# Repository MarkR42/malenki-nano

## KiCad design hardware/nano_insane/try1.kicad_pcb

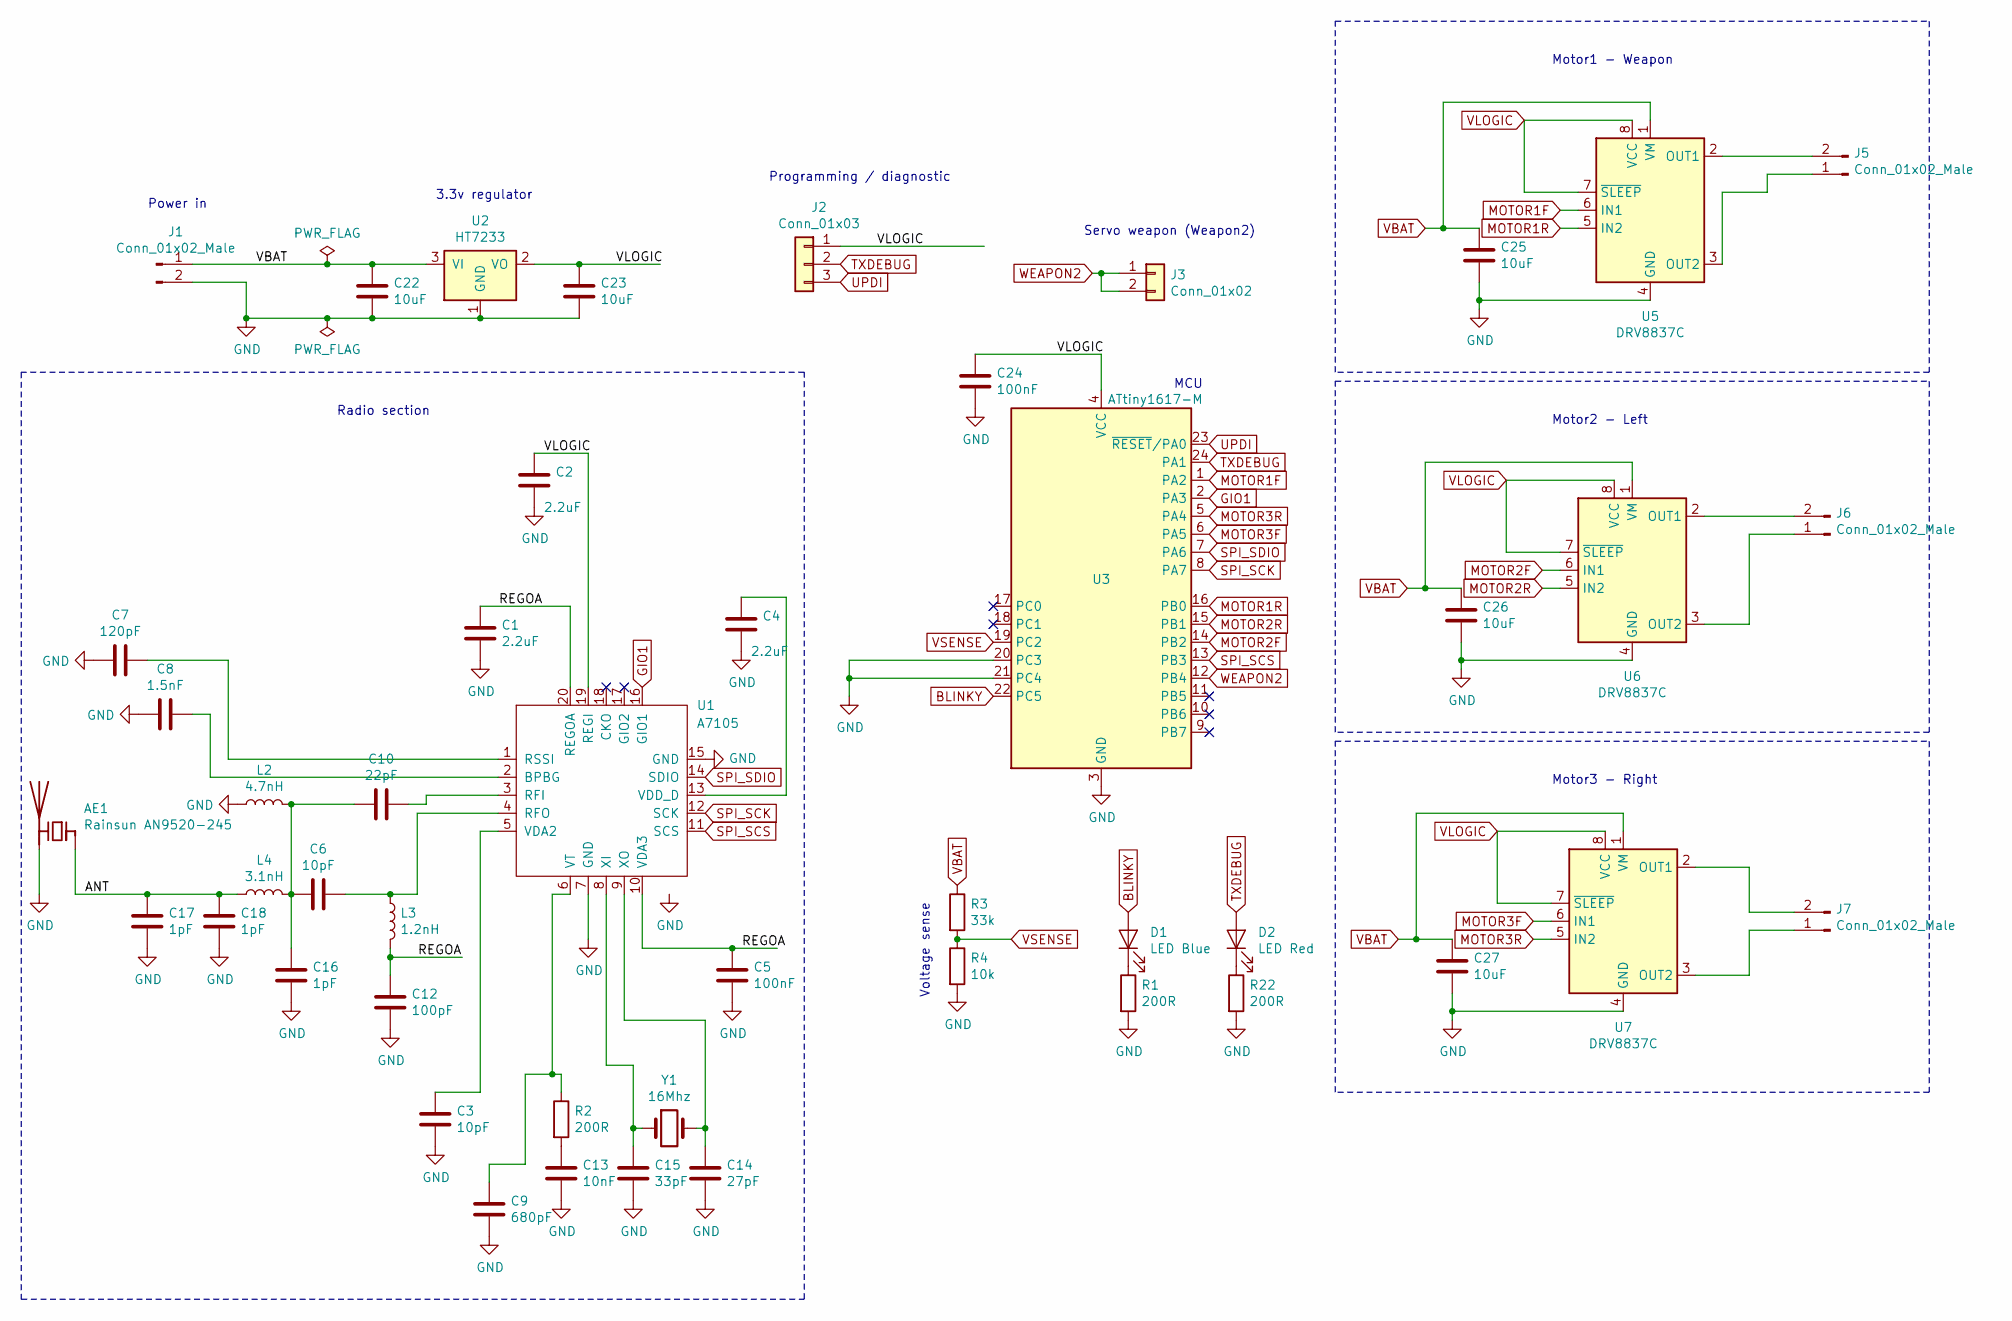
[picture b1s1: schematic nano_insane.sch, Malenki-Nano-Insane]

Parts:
AE1: Rainsun AN9520-245; Rainsun_AN9520
C1, C2, C4: 2.2uF; C_0402_1005Metric
C3, C6: 10pF; C_0402_1005Metric
C5: 100nF; C_0402_1005Metric
C7: 120pF; C_0402_1005Metric
C8: 1.5nF; C_0402_1005Metric
C9: 680pF; C_0402_1005Metric
C10: 22pF; C_0402_1005Metric
C12: 100pF; C_0402_1005Metric
C13: 10nF; C_0402_1005Metric
C14: 27pF; C_0402_1005Metric
C15: 33pF; C_0402_1005Metric
C16, C17, C18: 1pF; C_0402_1005Metric
C22, C23, C25, C26, C27: 10uF; C_0603_1608Metric; LCSC C19702
C24: 100nF; C_0402_1005Metric; Partnum C14663; LCSC C14663
D1: LED Blue; LED_0805_2012Metric_Castellated; LCSC C72035
D2: LED Red; LED_0805_2012Metric_Castellated; LCSC C84256
J1, J5, J6, J7: Conn_01x02_Male; PinHeader_1x02_P2.54mm_BIG1
J2: Conn_01x03; PinHeader_1x03_P2.00mm_Vertical
J3: Conn_01x02; wirepad_2
L2: 4.7nH; L_0402_1005Metric
L3: 1.2nH; L_0402_1005Metric
L4: 3.1nH; L_0402_1005Metric
R1, R2, R22: 200R; R_0402_1005Metric; Partnum C22962; LCSC C22962
R3: 33k; R_0402_1005Metric; Partnum C4216; LCSC C4216
R4: 10k; R_0402_1005Metric; Partnum C25804; LCSC C25804
U1: A7105; A7105_QFN-20
U2: HT7233; SOT-23; Partnum C211659; LCSC C211659
U3: ATtiny1617-M; qfn24-hand1; Partnum C194193; LCSC C194193
U5, U6, U7: DRV8837C; WSON-8-1EP_2x2mm_P0.5mm_HAND1; LCSC C39159
Y1: 16Mhz; Crystal_SMD_5032-2Pin_5.0x3.2mm

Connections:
/ANT: AE1.1 (FEED), C17.2, C18.2, L4.1
/REGOA: C1.2, C5.2, C12.2, L3.2, U1.10 (VDA3), U1.20 (REGOA)
BLINKY: D1.2 (A), U3.22 (PC5)
GIO1: U1.16 (GIO1), U3.2 (PA3)
GND: AE1.2 (PCB_Trace), C1.1, C2.1, C3.1, C4.1, C5.1, C7.2, C8.2, C9.1, C12.1, C13.1, C14.1, C15.1, C16.1, C17.1, C18.1, C22.2, C23.2, C24.2, C25.2, C26.2, C27.2, J1.2, L2.1, R1.2, R4.2, R22.2, U1.7 (GND), U1.15 (GND), U1.21 (GND), U2.1 (GND), U3.3 (GND), U3.20 (PC3), U3.21 (PC4), U3.25 (GND), U5.4 (GND), U5.9 (GND), U6.4 (GND), U6.9 (GND), U7.4 (GND), U7.9 (GND)
MOTOR1F: U3.1 (PA2), U5.6 (IN1)
MOTOR1R: U3.16 (PB0), U5.5 (IN2)
MOTOR2F: U3.14 (PB2), U6.6 (IN1)
MOTOR2R: U3.15 (PB1), U6.5 (IN2)
MOTOR3F: U3.6 (PA5), U7.6 (IN1)
MOTOR3R: U3.5 (PA4), U7.5 (IN2)
unnamed: C3.2, U1.5 (VDA2)
unnamed: C4.2, U1.13 (VDD_D)
unnamed: C6.1, L3.1, U1.4 (RFO)
unnamed: C7.1, U1.1 (RSSI)
unnamed: C8.1, U1.2 (BPBG)
unnamed: C9.2, R2.1, U1.6 (VT)
unnamed: C10.1, U1.3 (RFI)
unnamed: C6.2, C10.2, C16.2, L2.2, L4.2
unnamed: C13.2, R2.2
unnamed: C14.2, U1.9 (XO), Y1.2
unnamed: C15.2, U1.8 (XI), Y1.1
unnamed: D1.1 (K), R1.1
unnamed: D2.1 (K), R22.1
unnamed: J5.1, U5.3 (OUT2)
unnamed: J5.2, U5.2 (OUT1)
unnamed: J6.1, U6.3 (OUT2)
unnamed: J6.2, U6.2 (OUT1)
unnamed: J7.1, U7.3 (OUT2)
unnamed: J7.2, U7.2 (OUT1)
SPI_SCK: U1.12 (SCK), U3.8 (PA7)
SPI_SCS: U1.11 (SCS), U3.13 (PB3)
SPI_SDIO: U1.14 (SDIO), U3.7 (PA6)
TXDEBUG: D2.2 (A), J2.2, U3.24 (PA1)
UPDI: J2.3, U3.23 (~RESET~/PA0)
VBAT: C22.1, C25.1, C26.1, C27.1, J1.1, R3.1, U2.3 (VI), U5.1 (VM), U6.1 (VM), U7.1 (VM)
VLOGIC: C2.2, C23.1, C24.1, J2.1, U1.19 (REGI), U2.2 (VO), U3.4 (VCC), U5.7 (~SLEEP), U5.8 (VCC), U6.7 (~SLEEP), U6.8 (VCC), U7.7 (~SLEEP), U7.8 (VCC)
VSENSE: R3.2, R4.1, U3.19 (PC2)
WEAPON2: J3.1, J3.2, U3.12 (PB4)

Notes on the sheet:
Power in
3.3v regulator
MCU
Programming / diagnostic
Motor1 - Weapon
Motor2 - Left
Motor3 - Right
Servo weapon (Weapon2)
Voltage sense
Radio section

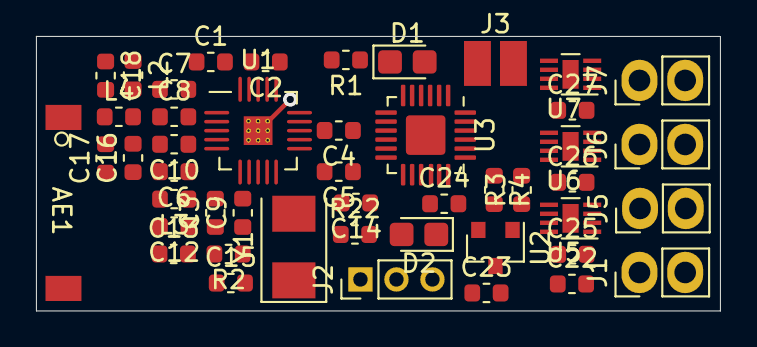
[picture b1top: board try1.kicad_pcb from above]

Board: 2 copper layers, 38.0 x 15.2 mm, 47 parts (0 on the bottom side), 39 nets.

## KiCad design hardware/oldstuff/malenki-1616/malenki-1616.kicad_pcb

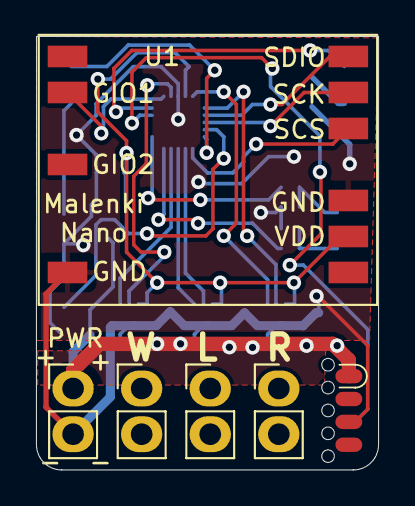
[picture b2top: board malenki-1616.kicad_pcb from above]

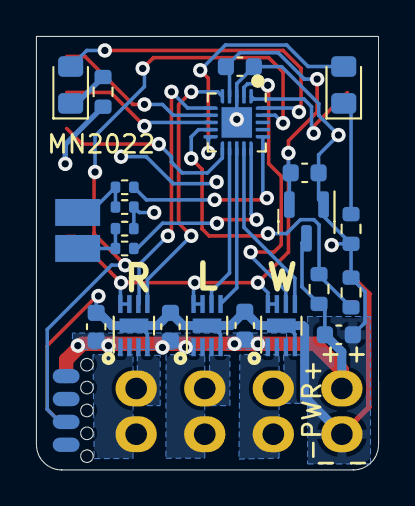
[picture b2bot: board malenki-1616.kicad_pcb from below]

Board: 2 copper layers, 19.0 x 24.1 mm, 28 parts (22 on the bottom side), 29 nets.

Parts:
C2, C3, C5, C6, C7: 10uF 25V; C_0603_1608Metric
C4: 0.1uF; C_0603_1608Metric
D1: LED Blue; LED_0805_2012Metric_Pad1.15x1.40mm_HandSolder
D2: LED Red; LED_0805_2012Metric_Pad1.15x1.40mm_HandSolder
J1, J5, J6, J7: Conn_01x02_Male; PinHeader_1x02_P2.54mm_BIG1
J2: Conn_01x08_Male; SOIC_clipProgSmall
J3: Conn_01x02; wirepad_2
R1, R2: 220R; R_0603_1608Metric
R3: 33k; R_0603_1608Metric
R4: 10k; R_0603_1608Metric
R5, R6: 470R; R_0402_1005Metric
R7, R8: 10k; R_0402_1005Metric
U1: A7105-MODULE; A7105-module
U2: AP2210N-3.3TRG1; SOT-23
U3: ATtiny1616-M; VQFN-20-1EP_3x3mm_P0.4mm_EP1.7x1.7mm
U5, U6, U7: DRV8837DSGR; WSON-8-1EP_2x2mm_P0.5mm_HAND1

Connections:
/W2: R5.2, U3.15 (PC0)
/W3: R6.2, U3.16 (PC1)
BLINKY: D1.2 (A), U3.10 (PB4)
GIO1: U1.2 (GIO1), U3.1 (PA2)
GND: C2.2, C3.2, C4.2, C5.2, C6.2, C7.2, J1.2, J2.3, R1.2, R2.2, R4.2, R7.1, R8.1, U1.7 (GND), U1.10 (GND), U2.1 (GND), U3.3 (GND), U3.21 (GND), U5.4 (GND), U5.9 (GND), U6.4 (GND), U6.9 (GND), U7.4 (GND), U7.9 (GND)
MOTOR1F: U3.2 (PA3), U5.6 (IN1)
MOTOR1R: U3.14 (PB0), U5.5 (IN2)
MOTOR2F: U3.12 (PB2), U6.6 (IN1)
MOTOR2R: U3.13 (PB1), U6.5 (IN2)
MOTOR3F: U3.6 (PA5), U7.6 (IN1)
MOTOR3R: U3.5 (PA4), U7.5 (IN2)
unnamed: D1.1 (K), R1.1
unnamed: D2.1 (K), R2.1
unnamed: J5.1, U5.3 (OUT2)
unnamed: J5.2, U5.2 (OUT1)
unnamed: J6.1, U6.3 (OUT2)
unnamed: J6.2, U6.2 (OUT1)
unnamed: J7.1, U7.3 (OUT2)
unnamed: J7.2, U7.2 (OUT1)
SPI_SCK: U1.13 (SCK), U3.8 (PA7)
SPI_SCS: U1.12 (SCS), U3.11 (PB3)
SPI_SDIO: U1.14 (SDIO), U3.7 (PA6)
TXDEBUG: D2.2 (A), U3.20 (PA1)
UPDI: J2.6, U3.19 (~RESET/PA0)
VBAT: C2.1, C5.1, C6.1, C7.1, J1.1, J2.1, R3.1, U2.3 (VI), U5.1 (VM), U6.1 (VM), U7.1 (VM)
VLOGIC: C3.1, C4.1, U1.9 (VDD), U2.2 (VO), U3.4 (VCC), U5.7 (~SLEEP), U5.8 (VCC), U6.7 (~SLEEP), U6.8 (VCC), U7.7 (~SLEEP), U7.8 (VCC)
VSENSE: R3.2, R4.1, U3.9 (PB5)
WEAPON2: J3.2, R5.1, R7.2
WEAPON3: J3.1, R6.1, R8.2
